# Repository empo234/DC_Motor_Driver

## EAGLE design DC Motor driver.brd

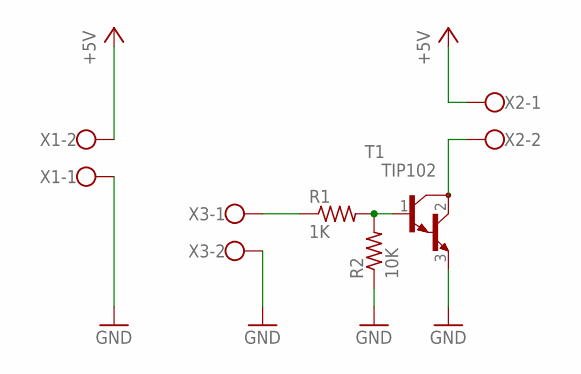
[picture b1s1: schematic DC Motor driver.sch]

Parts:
R1: 1K; 0309/12
R2: 10K; 0309/12
T1: TIP102; TO220
X1, X2, X3: W237-102

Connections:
+5V: X1.2, X2.1
GND: R2.1, T1.3 (E), X1.1, X3.2
unnamed: T1.2 (C), X2.2
unnamed: R1.2, R2.2, T1.1 (B)
unnamed: R1.1, X3.1

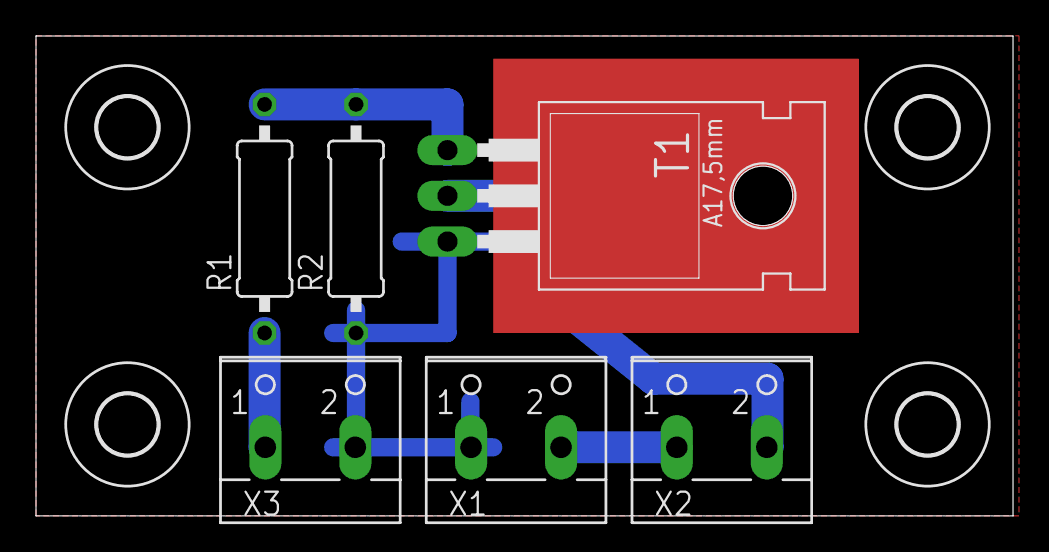
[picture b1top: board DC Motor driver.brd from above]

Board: 2 copper layers, 54.3 x 26.7 mm, 10 parts (0 on the bottom side), 5 nets.

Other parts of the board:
U$1, U$2, U$3, U$4: 3,3
